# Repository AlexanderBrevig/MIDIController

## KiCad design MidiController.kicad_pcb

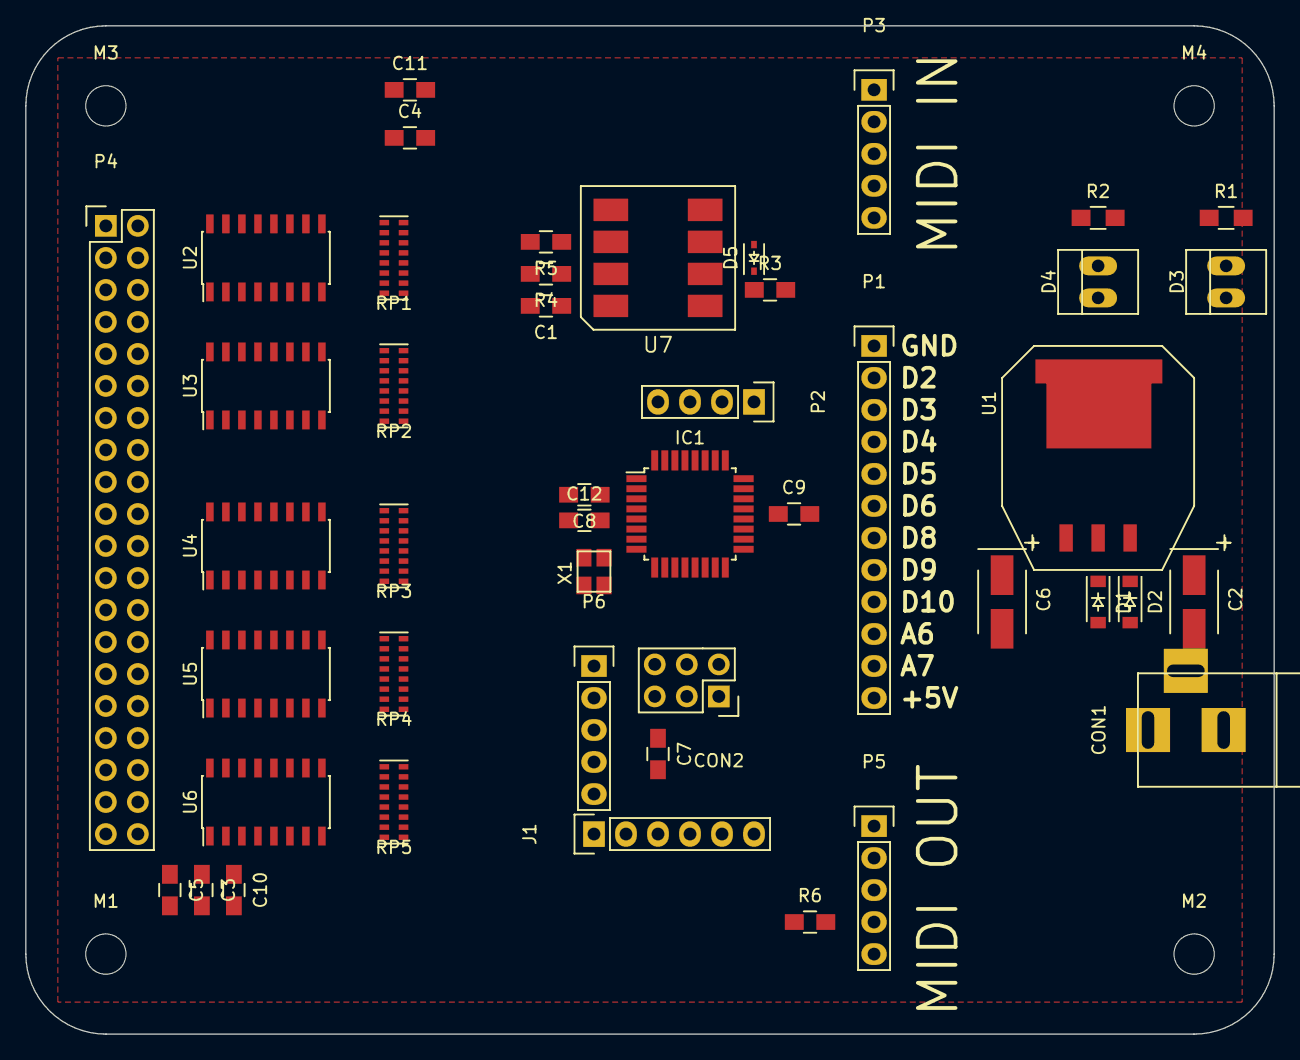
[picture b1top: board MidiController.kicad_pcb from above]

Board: 2 copper layers, 99.1 x 80.0 mm, 50 parts (0 on the bottom side), 80 nets, no tracks yet.

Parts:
C1, C3, C4, C5, C7, C8, C9, C10, C11, C12: 100nF; C_0805_HandSoldering
C2, C6: 100nF; TantalC_SizeB_EIA-3528_HandSoldering
CON1: BARREL_JACK
CON2: AVR-ISP-6; Socket_Strip_Straight_2x03
D1: D_Small; SOD-123
D2: ZENERsmall; SOD-123
D3: ONLED; PINHEAD1-2
D4: LED; PINHEAD1-2
D5: 1N914BWS; SOD-323
IC1: ATMEGA328P-A; TQFP-32_7x7mm_Pitch0.8mm
J1: FTDI_Basic; Pin_Header_Straight_1x06
M1, M2, M3, M4: 3M; MountingHole_3.2mm_M3
P1: CONN_01X12; Pin_Header_Straight_1x12
P2: CONN_01X04; Pin_Header_Straight_1x04
P3: MIDI_IN; Pin_Header_Straight_1x05
P4: CONN_02X20; Pin_Header_Straight_2x20
P5: MIDI_OUT; Pin_Header_Straight_1x05
P6: CONN_01X05; Pin_Header_Straight_1x05
R1, R2: R; R_0805_HandSoldering
R3, R4, R5, R6: 220; C_0805_HandSoldering
RP1, RP2, RP3, RP4, RP5: R_PACK8; R_Cat16-8
U1: LM1084IS-5.0/NOPB; TO-263
U2, U3, U4, U5, U6: 74LS165; SOIC-16_3.9x9.9mm_Pitch1.27mm
U7: 6N136SDVM; 6N136S
X1: CRYSTAL_SMD; crystal_FA238-TSX3225

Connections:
+5V: C1.1, C3.1, C4.1, C5.1, C6.1, C8.1, C9.1, C10.1, C11.1, C12.2, CON2.2, IC1.4, IC1.6, IC1.18, IC1.20, J1.3, P1.12, P2.4, P4.40, P6.5, R1.1, R5.2, R6.1, U1.2, U2.16, U3.16, U4.16, U5.16, U6.16, U7.8
/ADC6: IC1.19, P1.10
/ADC7: IC1.22, P1.11
/AUX2: IC1.32, P1.2
/AUX3: IC1.1, P1.3
/AUX4: IC1.2, P1.4
/AUX5: IC1.9, P1.5
/AUX6: IC1.10, P1.6
/AUX8: IC1.12, P1.7
/AUX9: IC1.13, P1.8
/AUX10: IC1.14, P1.9
/CE: IC1.24, U2.15, U3.15, U4.15, U5.15, U6.15
/CP: IC1.26, U2.2, U3.2, U4.2, U5.2, U6.2
/DIN: IC1.25, U6.9
/MISO: CON2.1, IC1.16, P6.3
/MOSI: CON2.4, IC1.15, P6.2
/PL: IC1.23, U2.1, U3.1, U4.1, U5.1, U6.1
/RST: C7.1, CON2.5, IC1.29
/RX: IC1.30, J1.4, R5.1, U7.6
/SCK: CON2.3, IC1.17, P6.4
/SCL: IC1.28, P2.3
/SDA: IC1.27, P2.2
/TX: IC1.31, J1.5, P5.5
GND: C1.2, C2.2, C3.2, C4.2, C5.2, C6.2, C8.2, C9.2, C10.2, C11.2, C12.1, CON1.2, CON1.3, CON2.6, D2.2, D3.1, D4.1, IC1.3, IC1.5, IC1.21, J1.1, J1.2, M1.1, M2.1, M3.1, M4.1, P1.1, P2.1, P5.2, P6.1, R4.2, RP1.9, RP1.10, RP1.11, RP1.12, RP1.13, RP1.14, RP1.15, RP1.16, RP2.9, RP2.10, RP2.11, RP2.12, RP2.13, RP2.14, RP2.15, RP2.16, RP3.9, RP3.10, RP3.11, RP3.12, RP3.13, RP3.14, RP3.15, RP3.16, RP4.9, RP4.10, RP4.11, RP4.12, RP4.13, RP4.14, RP4.15, RP4.16, RP5.9, RP5.10, RP5.11, RP5.12, RP5.13, RP5.14, RP5.15, RP5.16, U1.1, U2.8, U2.10, U3.8, U4.8, U5.8, U6.8, U7.5, X1.3
unnamed: C2.1, D1.1, D2.1, U1.3
unnamed: C7.2, J1.6
unnamed: CON1.1, D1.2
unnamed: D3.2, R1.2
unnamed: D4.2, R2.2
unnamed: D5.1, R3.1, U7.2
unnamed: D5.2, P3.5, U7.3
unnamed: IC1.7, X1.2
unnamed: IC1.8, X1.1
unnamed: IC1.11, R2.1
unnamed: P3.4, R3.2
unnamed: P4.1, RP1.1, U2.11
unnamed: P4.2, RP1.2, U2.12
unnamed: P4.3, RP1.3, U2.13
unnamed: P4.4, RP1.4, U2.14
unnamed: P4.5, RP1.5, U2.3
unnamed: P4.6, RP1.6, U2.4
unnamed: P4.7, RP1.7, U2.5
unnamed: P4.8, RP1.8, U2.6
unnamed: P4.9, RP2.1, U3.11
unnamed: P4.10, RP2.2, U3.12
unnamed: P4.11, RP2.3, U3.13
unnamed: P4.12, RP2.4, U3.14
unnamed: P4.13, RP2.5, U3.3
unnamed: P4.14, RP2.6, U3.4
unnamed: P4.15, RP2.7, U3.5
unnamed: P4.16, RP2.8, U3.6
unnamed: P4.17, RP3.1, U4.11
unnamed: P4.18, RP3.2, U4.12
unnamed: P4.19, RP3.3, U4.13
unnamed: P4.20, RP3.4, U4.14
unnamed: P4.21, RP3.5, U4.3
unnamed: P4.22, RP3.6, U4.4
unnamed: P4.23, RP3.7, U4.5
unnamed: P4.24, RP3.8, U4.6
unnamed: P4.25, RP4.1, U5.11
unnamed: P4.26, RP4.2, U5.12
unnamed: P4.27, RP4.3, U5.13
unnamed: P4.28, RP4.4, U5.14
unnamed: P4.29, RP4.5, U5.3
unnamed: P4.30, RP4.6, U5.4
unnamed: P4.31, RP4.7, U5.5
unnamed: P4.32, RP4.8, U5.6
unnamed: P4.33, RP5.1, U6.11
unnamed: P4.34, RP5.2, U6.12
unnamed: P4.35, RP5.3, U6.13
unnamed: P4.36, RP5.4, U6.14
unnamed: P4.37, RP5.5, U6.3
unnamed: P4.38, RP5.6, U6.4
unnamed: P4.39, RP5.7, U6.5
unnamed: P5.4, R6.2
unnamed: R4.1, U7.7
unnamed: U2.9, U3.10
unnamed: U3.9, U4.10
unnamed: U4.9, U5.10
unnamed: U5.9, U6.10

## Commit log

2017-03-09 rev 1.0
